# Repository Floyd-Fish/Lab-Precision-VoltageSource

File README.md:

# Lab-Precision-VoltageSource
A 18-bit Precision Bipolar DAC Module based on LTC2756&amp;LTC6655-2.5 with PMOD Interface

Article explaining the principle: https://www.emoe.xyz/precision-voltage-source-design/

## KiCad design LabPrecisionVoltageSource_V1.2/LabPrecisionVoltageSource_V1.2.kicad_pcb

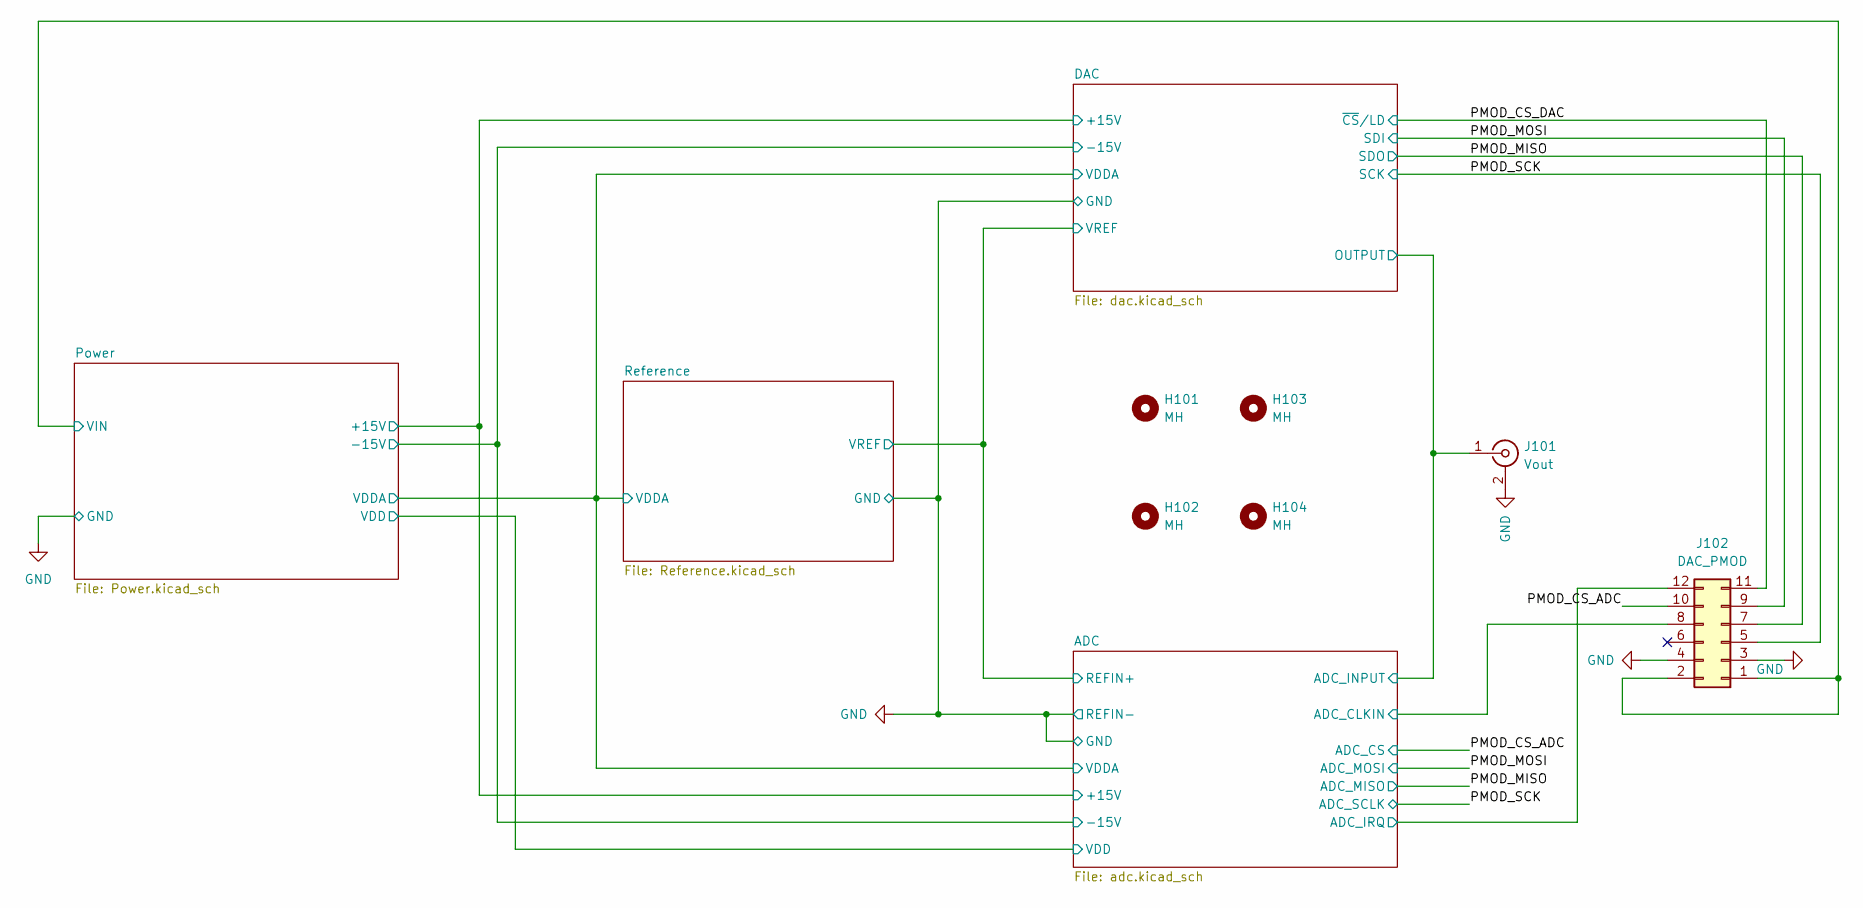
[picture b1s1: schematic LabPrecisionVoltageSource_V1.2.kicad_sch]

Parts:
H101, H102, H103, H104: MH; MountingHole_2.2mm_M2_ISO7380
J101: Vout; SMB_Jack_Vertical
J102: DAC_PMOD; PinSocket_2x06_P2.54mm_Vertical

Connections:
/ADC/ADC_CLKIN: J102.8; also elsewhere on the board
/ADC/ADC_INPUT: J101.1 (In); also elsewhere on the board
/ADC/ADC_IRQ: J102.12; also elsewhere on the board
/PMOD_CS_ADC: J102.10; also elsewhere on the board
/PMOD_CS_DAC: J102.11; also elsewhere on the board
/PMOD_MISO: J102.7; also elsewhere on the board
/PMOD_MOSI: J102.9; also elsewhere on the board
/PMOD_SCK: J102.5; also elsewhere on the board
GND: J101.2 (Ext), J102.3, J102.4; also elsewhere on the board
VIN: J102.1, J102.2; also elsewhere on the board

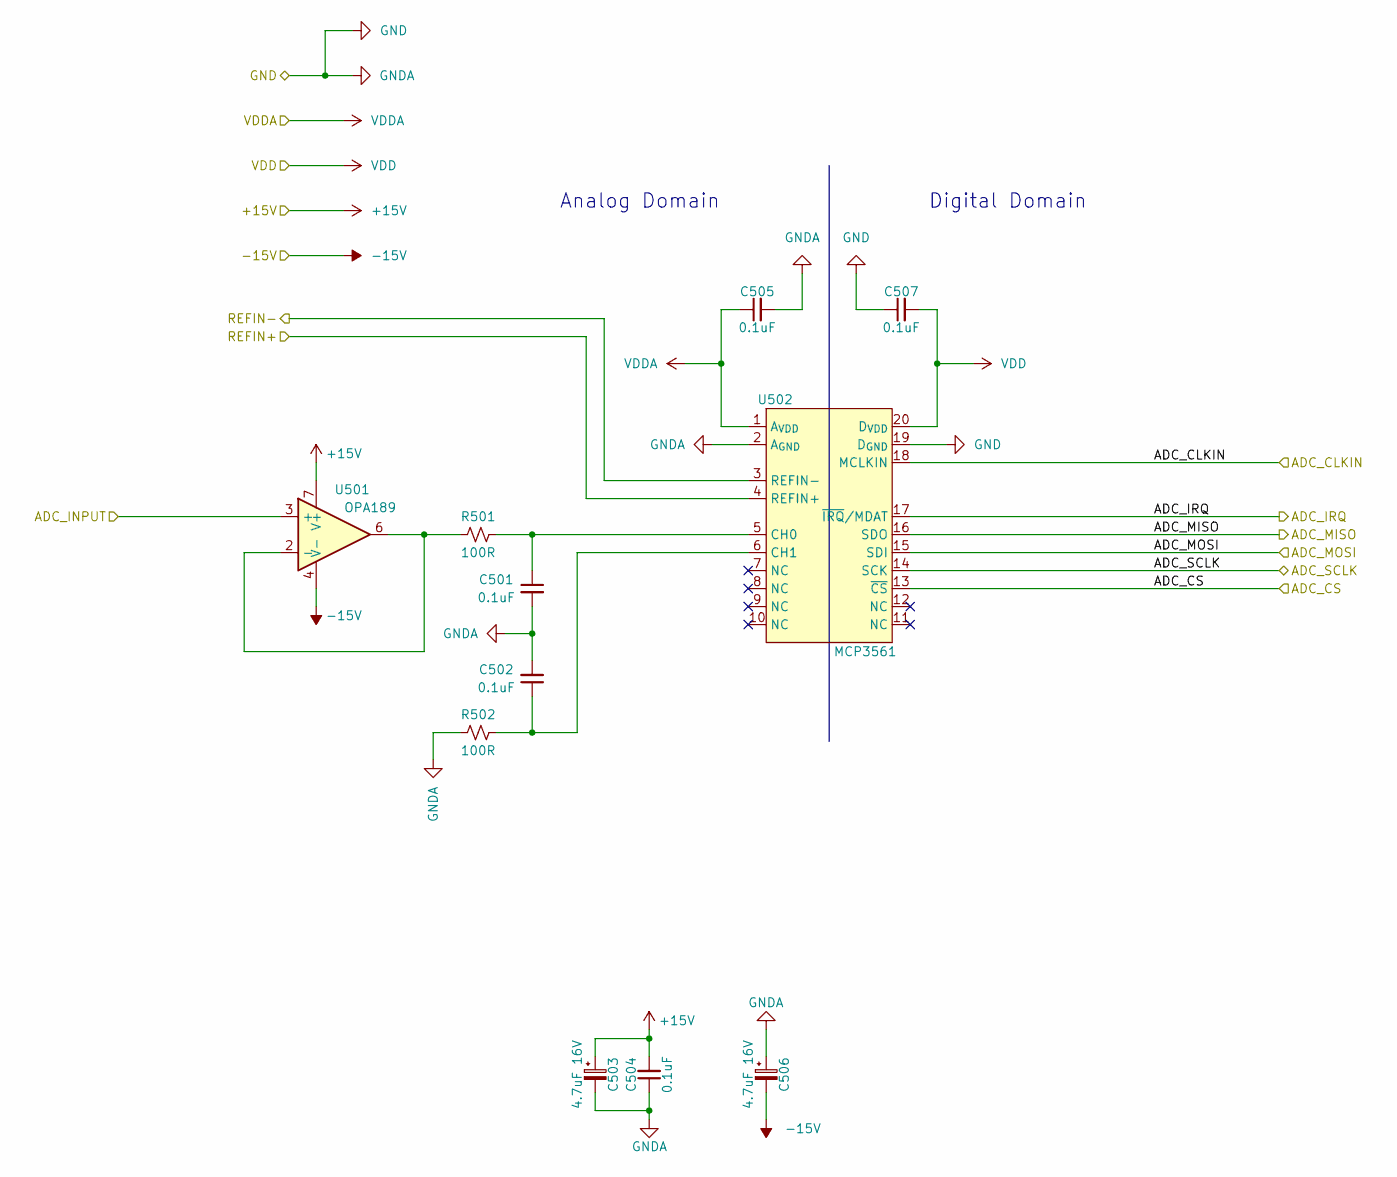
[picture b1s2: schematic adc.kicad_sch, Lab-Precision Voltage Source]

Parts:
C501, C502: 0.1uF; C_0402_1005Metric
C503, C506: 4.7uF 16V; CP_EIA-3216-10_Kemet-I
C504, C505, C507: 0.1uF; C_0603_1608Metric
R501, R502: 100R; R_0402_1005Metric
U501: OPA189; SOIC-8_3.9x4.9mm_P1.27mm
U502: MCP3561; TSSOP-20_4.4x6.5mm_P0.65mm

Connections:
+15V: C503.1, C504.2, U501.7 (V+); also elsewhere on the board
-15V: C506.2, U501.4 (V-); also elsewhere on the board
/ADC/ADC_CLKIN: U502.18 (MCLKIN); also elsewhere on the board
/ADC/ADC_INPUT: U501.3 (+); also elsewhere on the board
/ADC/ADC_IRQ: U502.17 (~IRQ/MDAT); also elsewhere on the board
/PMOD_CS_ADC: U502.13 (~CS); also elsewhere on the board
/PMOD_MISO: U502.16 (SDO); also elsewhere on the board
/PMOD_MOSI: U502.15 (SDI); also elsewhere on the board
/PMOD_SCK: U502.14 (SCK); also elsewhere on the board
/Reference/VREF: U502.4 (REFIN+); also elsewhere on the board
GND: C501.2, C502.2, C503.2, C504.1, C505.2, C506.1, C507.1, R502.2, U502.2 (A_{GND}), U502.3 (REFIN-), U502.19 (D_{GND}); also elsewhere on the board
unnamed: C501.1, R501.1, U502.5 (CH0)
unnamed: C502.1, R502.1, U502.6 (CH1)
unnamed: R501.2, U501.2 (-), U501.6
VDD: C507.2, U502.20 (D_{VDD}); also elsewhere on the board
VDDA: C505.1, U502.1 (A_{VDD}); also elsewhere on the board

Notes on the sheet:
Analog Domain
Digital Domain

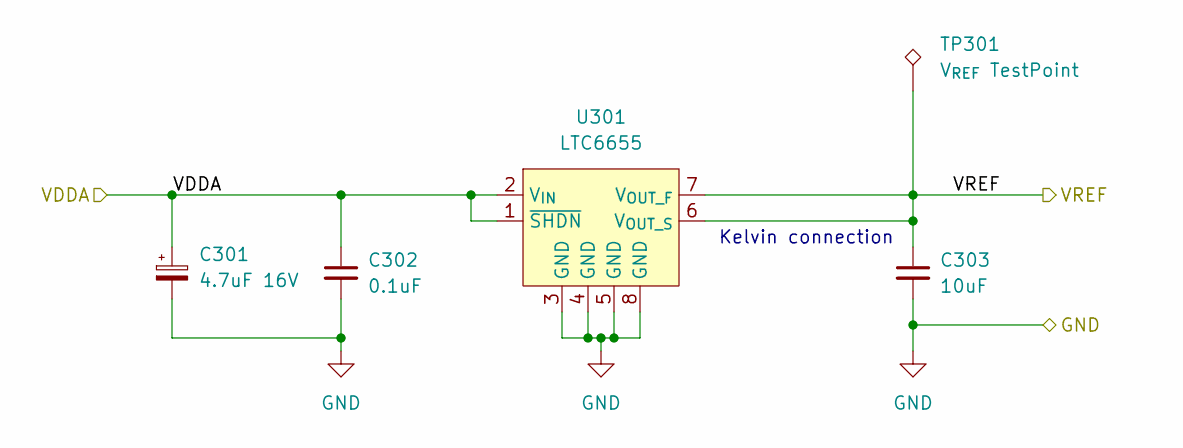
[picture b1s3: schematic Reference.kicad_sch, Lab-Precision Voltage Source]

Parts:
C301: 4.7uF 16V; CP_EIA-3216-10_Kemet-I
C302: 0.1uF; C_0603_1608Metric
C303: 10uF; C_0805_2012Metric
TP301: V_{REF} TestPoint; TestPoint_Pad_D1.0mm
U301: LTC6655; Linear_LS8

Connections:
/Reference/VREF: C303.1, TP301.1, U301.6 (V_{OUT_S}), U301.7 (V_{OUT_F}); also elsewhere on the board
GND: C301.2, C302.2, C303.2, U301.3 (GND), U301.4 (GND), U301.5 (GND), U301.8 (GND); also elsewhere on the board
VDDA: C301.1, C302.1, U301.1 (~SHDN), U301.2 (V_{IN}); also elsewhere on the board

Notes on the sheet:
Kelvin connection

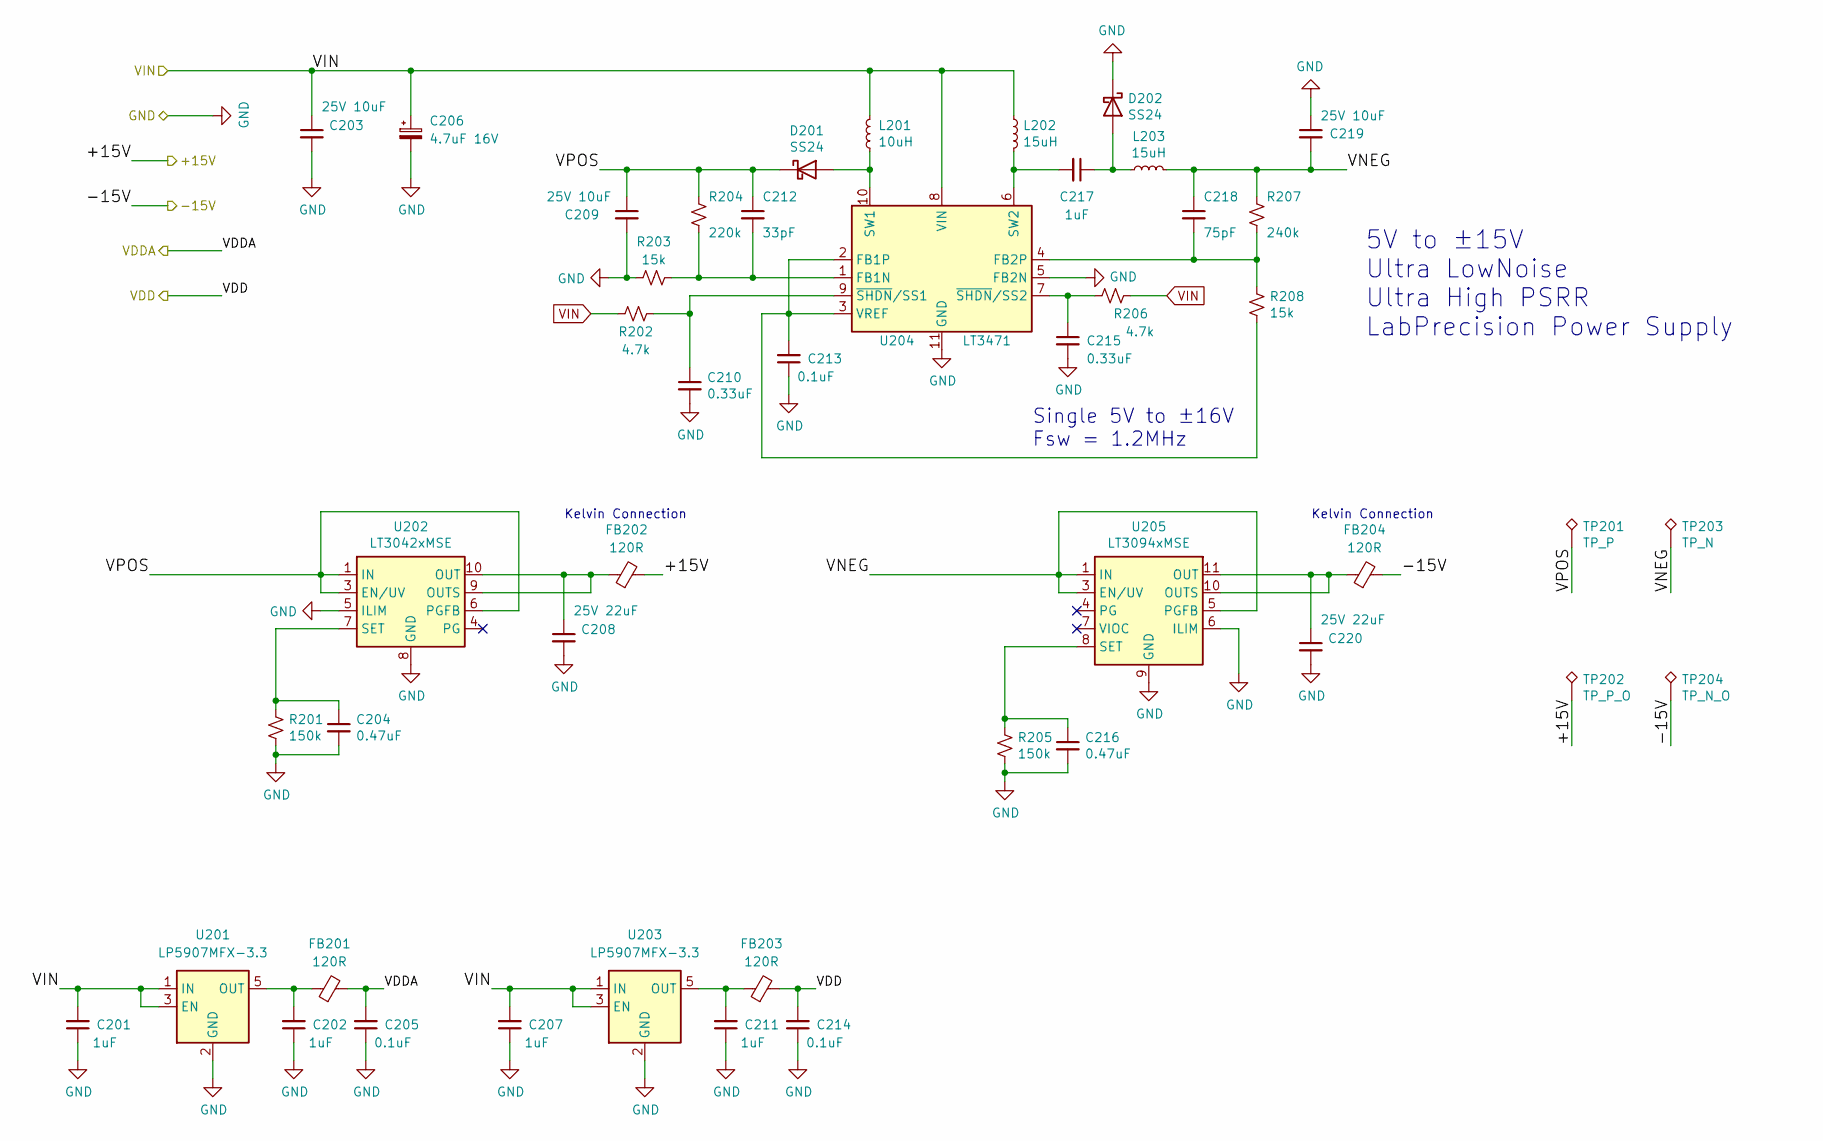
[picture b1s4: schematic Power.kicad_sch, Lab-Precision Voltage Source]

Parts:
C201, C202, C207, C211: 1uF; C_0603_1608Metric
C203, C209, C219: 25V 10uF; C_0805_2012Metric
C204, C216: 0.47uF; C_0402_1005Metric
C205, C214: 0.1uF; C_0603_1608Metric
C206: 4.7uF 16V; CP_EIA-3216-10_Kemet-I
C208, C220: 25V 22uF; C_0805_2012Metric
C210, C215: 0.33uF; C_0402_1005Metric
C212: 33pF; C_0402_1005Metric
C213: 0.1uF; C_0402_1005Metric
C217: 1uF; C_0805_2012Metric
C218: 75pF; C_0402_1005Metric
D201, D202: SS24; D_SOD-123F
FB201, FB202, FB203, FB204: 120R; L_0805_2012Metric
L201: 10uH; L_Bourns-SRN4018
L202, L203: 15uH; L_Bourns-SRN4018
R201, R205: 150k; R_0402_1005Metric
R202, R206: 4.7k; R_0402_1005Metric
R203, R208: 15k; R_0402_1005Metric
R204: 220k; R_0402_1005Metric
R207: 240k; R_0402_1005Metric
TP201: TP_P; TestPoint_Pad_D1.0mm
TP202: TP_P_O; TestPoint_Pad_D1.0mm
TP203: TP_N; TestPoint_Pad_D1.0mm
TP204: TP_N_O; TestPoint_Pad_D1.0mm
U201, U203: LP5907MFX-3.3; SOT-23-5
U202: LT3042xMSE; DFN-10-1EP_3x3mm_P0.5mm_EP1.65x2.38mm
U204: LT3471; DFN-10-1EP_3x3mm_P0.5mm_EP1.65x2.38mm
U205: LT3094xMSE; DFN-12-1EP_3x3mm_P0.45mm_EP1.66x2.38mm

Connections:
+15V: FB202.2, TP202.1; also elsewhere on the board
-15V: FB204.2, TP204.1; also elsewhere on the board
/Power/VNEG: C218.1, C219.2, L203.2, R207.2, TP203.1, U205.1 (IN), U205.2 (IN), U205.3 (EN/UV), U205.5 (PGFB), U205.13 (IN)
/Power/VPOS: C209.1, C212.1, D201.1 (K), R204.2, TP201.1, U202.1 (IN), U202.2 (IN), U202.3 (EN/UV), U202.6 (PGFB)
GND: C201.1, C202.1, C203.2, C204.2, C205.1, C206.2, C207.1, C208.2, C209.2, C210.2, C211.1, C213.1, C214.1, C215.2, C216.2, C219.1, C220.2, D202.1 (K), R201.1, R203.1, R205.1, U201.2 (GND), U202.5 (ILIM), U202.8 (GND), U202.11 (GND), U203.2 (GND), U204.5 (FB2N), U204.11 (GND), U205.6 (ILIM), U205.9 (GND); also elsewhere on the board
unnamed: C202.2, FB201.1, U201.5 (OUT)
unnamed: C204.1, R201.2, U202.7 (SET)
unnamed: C208.1, FB202.1, U202.9 (OUTS), U202.10 (OUT)
unnamed: C210.1, R202.2, U204.9 (~SHDN/SS1)
unnamed: C211.2, FB203.1, U203.5 (OUT)
unnamed: C212.2, R203.2, R204.1, U204.1 (FB1N)
unnamed: C213.2, R208.1, U204.2 (FB1P), U204.3 (VREF)
unnamed: C215.1, R206.1, U204.7 (~SHDN/SS2)
unnamed: C216.1, R205.2, U205.8 (SET)
unnamed: C217.1, D202.2 (A), L203.1
unnamed: C217.2, L202.2, U204.6 (SW2)
unnamed: C218.2, R207.1, R208.2, U204.4 (FB2P)
unnamed: C220.1, FB204.1, U205.10 (OUTS), U205.11 (OUT), U205.12 (OUT)
unnamed: D201.2 (A), L201.1, U204.10 (SW1)
VDD: C214.2, FB203.2; also elsewhere on the board
VDDA: C205.2, FB201.2; also elsewhere on the board
VIN: C201.2, C203.1, C206.1, C207.2, L201.2, L202.1, R202.1, R206.2, U201.1 (IN), U201.3 (EN), U203.1 (IN), U203.3 (EN), U204.8 (VIN); also elsewhere on the board

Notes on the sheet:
Kelvin Connection
Single 5V to ±16V Fsw = 1.2MHz
5V to ±15V Ultra LowNoise Ultra High PSRR LabPrecision Power Supply

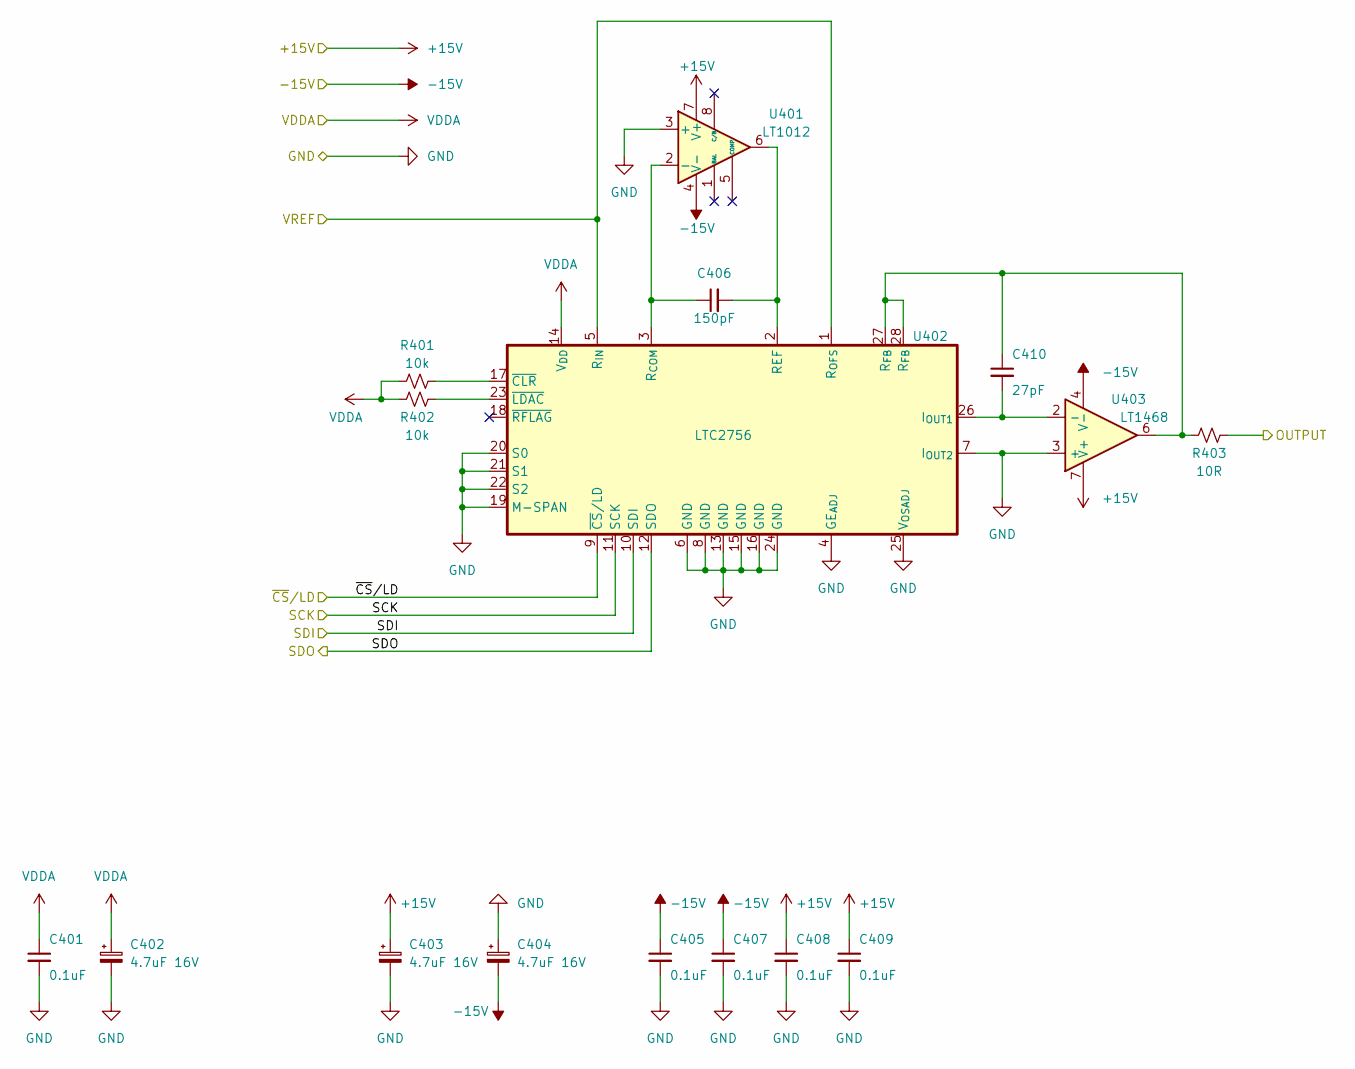
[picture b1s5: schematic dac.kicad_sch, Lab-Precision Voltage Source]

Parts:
C401, C405, C407, C408, C409: 0.1uF; C_0603_1608Metric
C402, C403, C404: 4.7uF 16V; CP_EIA-3216-10_Kemet-I
C406: 150pF; C_0402_1005Metric
C410: 27pF; C_0402_1005Metric
R401, R402: 10k; R_0603_1608Metric
R403: 10R; R_0603_1608Metric
U401: LT1012; SOIC-8_3.9x4.9mm_P1.27mm
U402: LTC2756; SSOP-28_5.3x10.2mm_P0.65mm
U403: LT1468; SOIC-8_3.9x4.9mm_P1.27mm

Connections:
+15V: C403.1, C408.1, C409.1, U401.7 (V+), U403.7 (V+); also elsewhere on the board
-15V: C404.2, C405.1, C407.1, U401.4 (V-), U403.4 (V-); also elsewhere on the board
/ADC/ADC_INPUT: R403.1; also elsewhere on the board
/PMOD_CS_DAC: U402.9 (~CS/LD); also elsewhere on the board
/PMOD_MISO: U402.12 (SDO); also elsewhere on the board
/PMOD_MOSI: U402.10 (SDI); also elsewhere on the board
/PMOD_SCK: U402.11 (SCK); also elsewhere on the board
/Reference/VREF: U402.1 (R_{OFS}), U402.5 (R_{IN}); also elsewhere on the board
GND: C401.2, C402.2, C403.2, C404.1, C405.2, C407.2, C408.2, C409.2, U401.3 (+), U402.4 (GE_{ADJ}), U402.6 (GND), U402.7 (I_{OUT2}), U402.8 (GND), U402.13 (GND), U402.15 (GND), U402.16 (GND), U402.19 (M-SPAN), U402.20 (S0), U402.21 (S1), U402.22 (S2), U402.24 (GND), U402.25 (V_{OSADJ}), U403.3 (+); also elsewhere on the board
unnamed: C406.1, U401.2 (-), U402.3 (R_{COM})
unnamed: C406.2, U401.6, U402.2 (REF)
unnamed: C410.1, R403.2, U402.27 (R_{FB}), U402.28 (R_{FB}), U403.6
unnamed: C410.2, U402.26 (I_{OUT1}), U403.2 (-)
unnamed: R401.1, U402.17 (~CLR)
unnamed: R402.1, U402.23 (~LDAC)
VDDA: C401.1, C402.1, R401.2, R402.2, U402.14 (V_{DD}); also elsewhere on the board

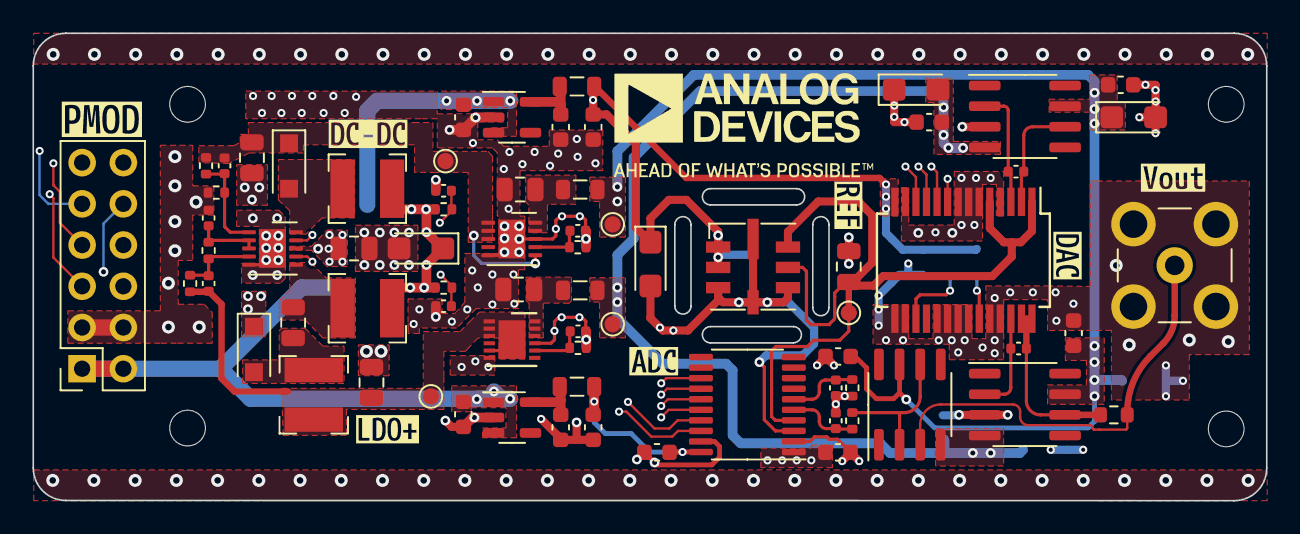
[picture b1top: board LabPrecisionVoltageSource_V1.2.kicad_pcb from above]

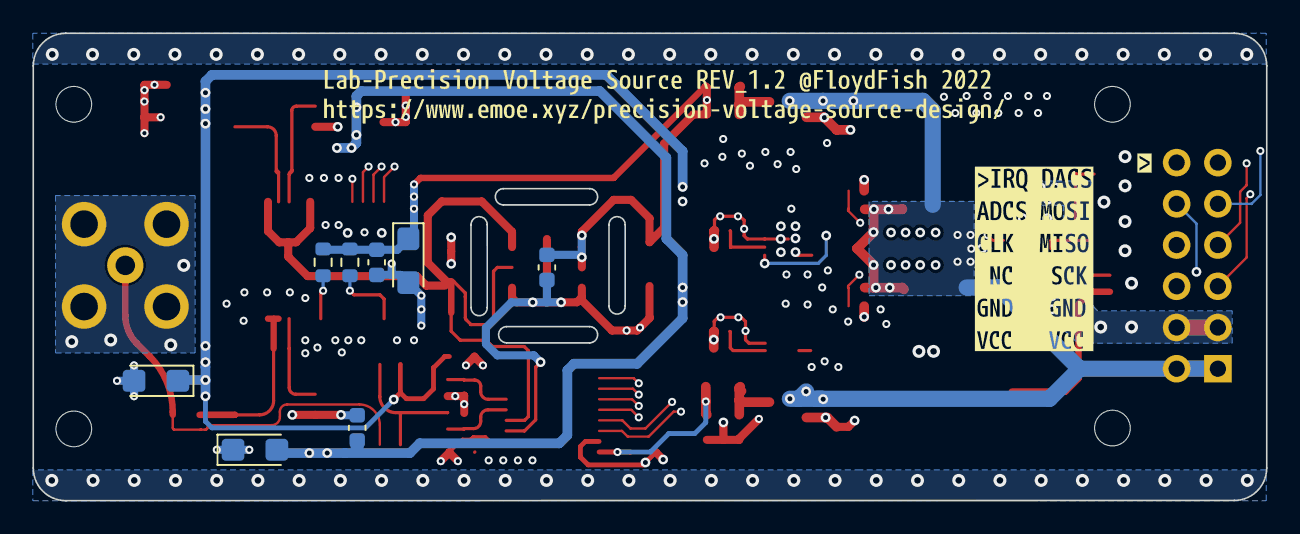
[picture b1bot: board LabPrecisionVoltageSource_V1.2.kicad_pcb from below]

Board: 4 copper layers, 76.0 x 28.8 mm, 96 parts (12 on the bottom side), 40 nets.

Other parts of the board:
kibuzzard-63418A0A: G***; kibuzzard-63418A0A
kibuzzard-63418A1A: G***; kibuzzard-63418A1A
kibuzzard-63418A4B: G***; kibuzzard-63418A4B
kibuzzard-63418A24: G***; kibuzzard-63418A24
kibuzzard-634188FD: G***; kibuzzard-634188FD
kibuzzard-634189C4: G***; kibuzzard-634189C4
kibuzzard-634189ED: G***; kibuzzard-634189ED
kibuzzard-634189F6: G***; kibuzzard-634189F6
kibuzzard-634189FF: G***; kibuzzard-634189FF
kibuzzard-6341896C: G***; kibuzzard-6341896C
kibuzzard-63418870: G***; kibuzzard-63418870
kibuzzard-63418876: G***; kibuzzard-63418876

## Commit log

2023-03-18 V1.2 Design File Upload
2023-03-18 Upload images

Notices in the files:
LabPrecisionVoltageSource_V1.2/adc.kicad_sch:
©Floydfish 2022
